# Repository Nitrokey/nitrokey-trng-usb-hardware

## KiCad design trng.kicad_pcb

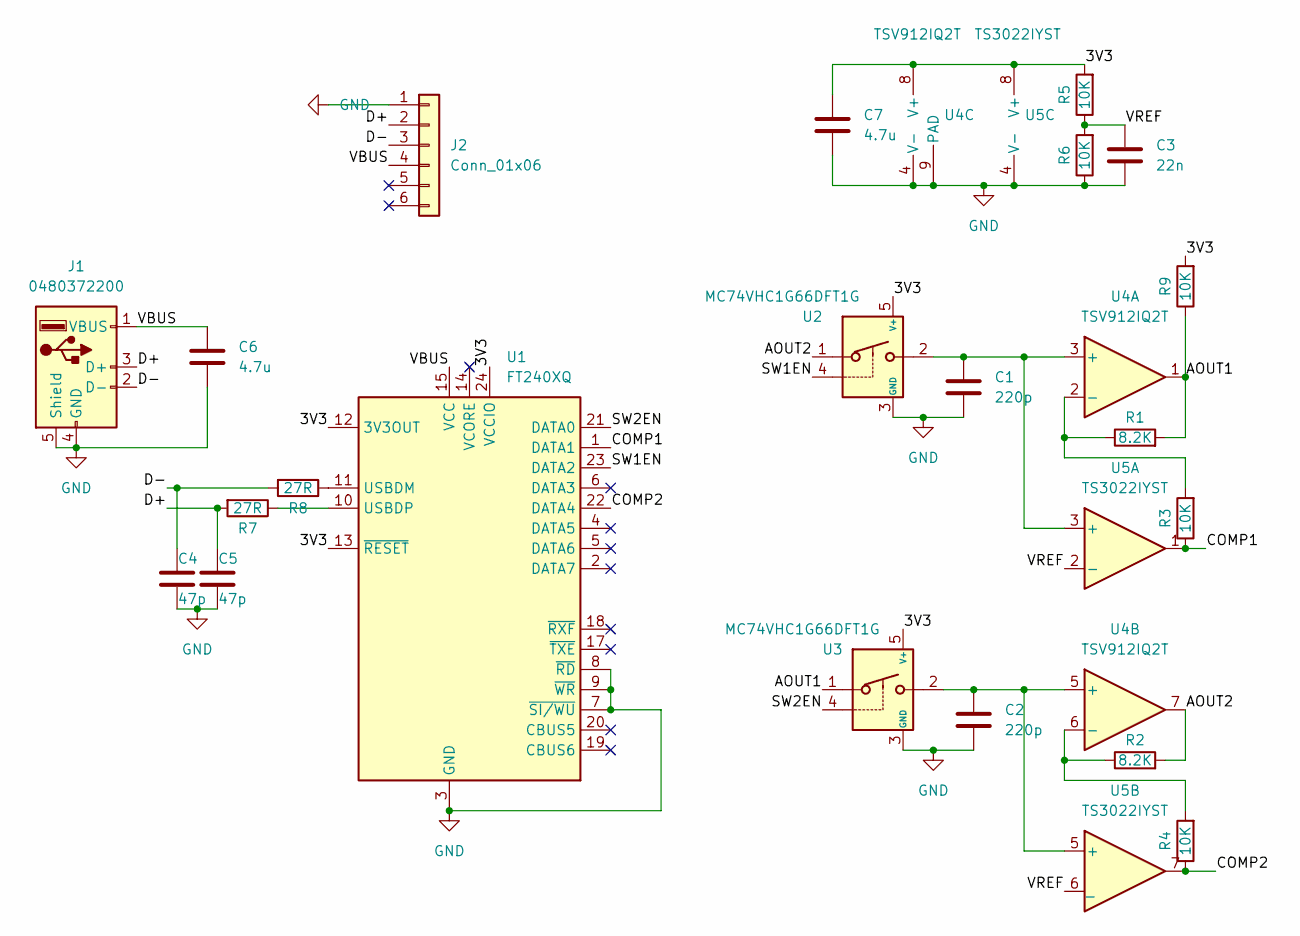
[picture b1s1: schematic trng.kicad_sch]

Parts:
C1, C2: 220p; C_0603_1608Metric
C3: 22n; C_0402_1005Metric
C4, C5: 47p; C_0402_1005Metric
C6, C7: 4.7u; C_0603_1608Metric
J1: 0480372200; USB-A-PLUG
J2: Conn_01x06; nitro_programming_header
R1, R2: 8.2K; R_0402_1005Metric
R3, R4, R5, R6, R9: 10K; R_0402_1005Metric
R7, R8: 27R; R_0402_1005Metric
U1: FT240XQ; QFN-24-1EP_4x4mm_P0.5mm_EP2.6x2.6mm
U2, U3: MC74VHC1G66DFT1G; SOT-353_SC-70-5
U4: TSV912IQ2T; DFN-8-1EP_2x2mm_P0.5mm_EP1.05x1.75mm
U5: TS3022IYST

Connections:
/3V3: C7.1, R5.2, R9.2, U1.12 (3V3OUT), U1.13 (~RESET), U1.24 (VCCIO), U2.5 (V+), U3.5 (V+), U4.8 (V+), U5.8 (V+)
/AOUT1: R1.2, R9.1, U3.1, U4.1
/AOUT2: R2.2, U2.1, U4.7
/COMP1: R3.1, U1.1 (DATA1), U5.1
/COMP2: R4.1, U1.22 (DATA4), U5.7
/D+: C5.1, J1.3 (D+), J2.2, R7.2
/D-: C4.1, J1.2 (D-), J2.3, R8.2
/SW1EN: U1.23 (DATA2), U2.4
/SW2EN: U1.21 (DATA0), U3.4
/VBUS: C6.1, J1.1 (VBUS), J2.4, U1.15 (VCC)
/VREF: C3.1, R5.1, R6.2, U5.2 (-), U5.6 (_)
GND: C1.2, C2.2, C3.2, C4.2, C5.2, C6.2, C7.2, J1.4 (GND), J1.5 (Shield), J2.1, R6.1, U1.3 (GND), U1.7 (~SI/WU), U1.8 (~RD), U1.9 (~WR), U1.16 (GND), U1.25 (GND), U2.3 (GND), U3.3 (GND), U4.4 (V-), U4.9 (PAD), U5.4 (V-)
unnamed: C1.1, U2.2, U4.3 (+), U5.3 (+)
unnamed: C2.1, U3.2, U4.5 (+), U5.5 (+)
unnamed: R1.1, R3.2, U4.2 (-)
unnamed: R2.1, R4.2, U4.6 (-)
unnamed: R7.1, U1.10 (USBDP)
unnamed: R8.1, U1.11 (USBDM)

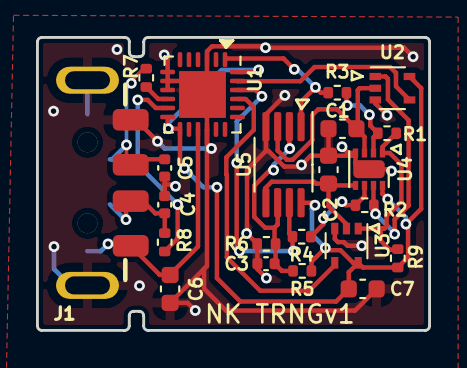
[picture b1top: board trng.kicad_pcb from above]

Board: 2 copper layers, 21.8 x 16.3 mm, 23 parts (1 on the bottom side), 18 nets.

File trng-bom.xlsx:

RD | Value | Footprint | Quantity | Manufacturer | MPN | URL
> C1, C2 | 220p 50V 5% C0G | Capacitor_SMD:C_0603_1608Metric | 2 | Murata | GRM1885C1H221JA01D | https://www.digikey.de/en/products/detail/GRM1885C1H221JA01D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
C3 | 22n C0G | Capacitor_SMD:C_0402_1005Metric | 1
> C4, C5 | 47p C0G | Capacitor_SMD:C_0402_1005Metric | 2
> C6, C7 | 4.7u 25V X7R | Capacitor_SMD:C_0603_1608Metric | 2
J1 | 480372200 | trng-parts:USB-A-PLUG | 1 | Molex | 480372200 | https://www.digikey.de/de/products/detail/molex/0480372200/2421361
> R1, R2 | 8.2K 1% | Resistor_SMD:R_0402_1005Metric | 2
> R3-R6, R9 | 10K 1% | Resistor_SMD:R_0402_1005Metric | 5
> R7, R8 | 27R 1% | Resistor_SMD:R_0402_1005Metric | 2
U1 | FT240XQ | Package_DFN_QFN:QFN-24-1EP_4x4mm_P0.5mm_EP2.6x2.6mm | 1 | FTDI | FT240XQ-T | https://www.digikey.de/en/products/detail/ftdi-future-techno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
> U2, U3 | MC74VHC1G66DFT1G | Package_TO_SOT_SMD:SOT-353_SC-70-5 | 2 | onsemi | MC74VHC1G66DFT1G | https://de.farnell.com/webapp/wcs/stores/servlet/ProductDisp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
U4 | TSV912IQ2T | Package_DFN_QFN:DFN-8-1EP_2x2mm_P0.5mm_EP1.05x1.75mm | 1 | ST | TSV912IQ2T | https://de.farnell.com/stmicroelectronics/tsv912iq2t/op-vers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
U5 | TS3022IYST | Package_SO:MSOP-8_3x3mm_P0.65mm | 1 | ST | TS3022IYST | https://www.digikey.de/en/products/detail/stmicroelectronics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

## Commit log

2022-04-08 Update schematic pdf, add BOM
2022-04-08 Add CERN-OHL-S license
2022-04-12 add panelized gerbers and production data
2022-06-23 Add test header and recreate production data
2022-08-19 BOM: Alternatives TSV7722IQ2T, MAX942EUA+ added
